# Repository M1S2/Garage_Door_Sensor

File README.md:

# Garage Door Sensor

This is a project to send the status of multiple garage doors (or equal) to one indoor station. This is useful if the door can't be seen from inside.
Each device (sensor and indoor station) uses an ESP12-F (ESP8266) controller that runs the software and is the WiFi transmitter. The data between the sensor and the indoor station is transmitted using ESP-Now. The indoor station acts as a gateway between ESP-Now and WiFi.

## Building the Indoor Station
You need to build only one indoor station. It receives the state of all door sensors. The current version of the indoor station is capable of displaying 2 sensors at the same time. If you need more sensors, the indoor station must be adapted.

### PCBs and Housing
The PCBs are designed using Autodesk Fusion360 to be manufactured with toner transfer method. All design files are located in the [Electrical files for IndoorStation](IndoorStation/Electrical) subfolder.

The housing parts are also designed using Autodesk Fusion360 to be manufactured with a 3D printer. All files are located in the [Mechanical files for IndoorStation](IndoorStation/Mechanical) subfolder. Each part is needed once except the Stand (needed twice).

Also the following additional parts are necessary:
- 4x Screw M3x20
- 2x Screw M3x10
- 6x Heat Insert M3x5x5
- some acrylic glass to cover and diffuse the LEDs
- DC Power Supply (voltage e.g. 5V, is regulated down to 3.3V)

The following image shows all parts of the IndoorStation:

### Software
The software files are located in the [Software files for IndoorStation](IndoorStation/Software) subfolder.

To build and flash the lastest software to the IndoorStation ESP12-F download and install Visual Studio Code and install the PlatformIO extension. The following page explains the whole process: https://randomnerdtutorials.com/vs-code-platformio-ide-esp32-esp8266-arduino/

The following parts must be flashed:
- Firmware: Use the `Build` and `Upload` PlatformIO tasks.
- Filesystem (containing the website files): Use the `Build Filesystem Image` and `Upload Filesystem Image` PlatformIO tasks.

## Building the Sensor
You need to build one sensor per door to monitor. The current version of the indoor station is capable of displaying 2 sensors at the same time. If you need more sensors, the indoor station must be adapted. No changes to the sensor are necessary.
### PCBs and Housing
The PCBs are designed using Autodesk Fusion360 to be manufactured with toner transfer method. All design files are located in the [Electrical files for sensor](Sensor/Electrical) subfolder.

The housing parts are also designed using Autodesk Fusion360 to be manufactured with a 3D printer. All files are located in the [Mechanical files for sensor](Sensor/Mechanical) subfolder. Each part is needed once.

Also the following additional parts are necessary:
- 4x Screw M3x30
- 4x Heat Inserts M3x5x5
- 1x Li-Ion 18650 (e.g. https://www.roboter-bausatz.de/p/bak-18650-lithium-ionen-akku-2900mah-3-6v-3-7v-erhoehter-pluspol)
- 1x Charge Modul USB-C (e.g. https://www.roboter-bausatz.de/p/lithium-batterie-lademodul-usb-c-ip2312-4-2v-5v)
- 2x Magnet for Door Mount

The following image shows all parts of the Sensor:

### Software
The software files are located in the [Software files for Sensor](Sensor/Software) subfolder.

To build and flash the lastest software to the sensor ESP12-F download and install Visual Studio Code and install the PlatformIO extension. The following page explains the whole process: https://randomnerdtutorials.com/vs-code-platformio-ide-esp32-esp8266-arduino/

## Usage
This chapter describes the basic usage of the indoor station and sensor. It is necessary to build at least one device each before proceding.
### Charging the sensor
Switch off the sensor via the switch on the back side and connect it to an USB-C charger. Make sure the charger is capable of delivering enough energy. Otherwise the charging process will be slow.

Charger LED states:

|LED		|Meaning		|
|---------------|-----------------------|
|Red solid	|Powered via USB-C	|
|Green solid	|Charging complete	|

### WiFi Setup
The indoor station isn't yet connected to your local WiFi the first time you use it or after a reset.
It is necessary to connect it to the WiFi. Otherwise the following steps can't be done and the indoor station can't receive the sensor messages.
1. Power the indoor station.
2. The WiFi LED will start flashing blue for about 5 seconds (indicating that it's trying to set up a connection).
3. After this timeout, the WiFi LED will change to white, indicating that the indoor station entered access point configuration mode.
4. Search for all available WiFi networks with your smartphone or computer and connect to the one called "Garagen Tor Status AP" (configuration access point).
5. After connecting to the configuration access point, a captive portal pops up automatically (sometimes needs some seconds; otherwise directly open the IP 192.168.4.1 in your browser).
6. Select your routers WiFi network and enter the password.
7. After confirmation, the indoor station restarts and the WiFi LED is flashing blue again until the connection to the router is established.
8. When successfully connected to the WiFi, the WiFi LED is solid blue.

### Pairing of the Sensor
The pairing of the sensor can be done via the pairing button of the indoor station and the pairing button of the corresponding sensor.
1. Press the pairing button on the indoor station long. The first sensor led will start to flash blue and red.
2. Press the pairing button on the indoor station short to select the sensor slot you want to pair.
3. When the indoor station mode for the correct sensor is pairing, press and hold the pairing button on the sensor for at least 5 seconds (sensor must be switched on).
4. If the pairing of the sensor was successful, the indoor station stopped to flash blue and red.

Repeat all steps for all sensors.

**Alternative:**

The pairing of the sensor can also be done via the web pages of the indoor station.
1. Open the web page (with one of the following ways):
   a) Enter the IP address that was assigned by your router in the address bar of your browser.
   b) For Fritz!Box: enter the following host name in the address bar of your browser: `garagen-tor-status.fritz.box` (or scan the QR code below)
2. Change to the configuration page (gear icon)
3. Enter the MAC address of the sensor to pair in the textbox of the corresponding sensor and click submit.
4. All messages of this sensor are now received for the sensor index where the MAC address was entered.

Repeat steps 3. and 4. for all sensors.

### Mounting the Sensor and Magnet
To mount the sensor and magnet to the garage door:
1. Insert a magnet inside the `Magnet_Mount` part and assemble the `Magnet_Mount_Lid` with a screw.
2. Take the full assembled sensor, the `Door_Mount` part and the `Magnet_Mount`.
3. Switch off the sensor using the switch on the back side.
4. Go inside the garage and close the door.
5. Fix the `Door_Mount` part with double sided tape or power stripes to the door frame. Make sure, there is a small gap of about 3 mm to the metal blade of the door (the outermost moving part). An example position is shown in the following pictures:
6. Insert the sensor in the `Door_Mount`. The two magnets on the `Door_Mount` hold the sensor in place. The counterparts are the two upper screws in the sensor housing.
7. Fix the `Magnet_Mount` part with double sided tape or power stripes to the door blade. Make sure, the magnet is near the icon on the side of the sensor (indicating the position of the reed switch).
8. Open and close the door to make sure, the magnet is moved from and to the sensor, without any mechanical contact. If the door is closed, the magnet must reside near the sensor again.
9. Remove the sensor from the `Door_Mount`, switch the sensor on using the switch on the back side and insert the sensor in the `Door_Mount` again.

<p>
  </img>
  </img>
</p>

### Testing
To test the whole system, open and close one garage door after another and monitor the displayed state on the indoor station.
- When the first door is closed, the LED "1" on the indoor station will be red.
- When the first door is open, the LED "1" on the indoor station will be green.
- When the second door is closed, the LED "2" on the indoor station will be red.
- When the second door is open, the LED "2" on the indoor station will be green.
- All actual door states can also be monitored via the web page (overview page). To open the the web page, follow the steps at the ["Pairing the sensor" chapter](#pairing-of-the-sensor).

## LED States
| Led		         | Color 	    | State    | Description						                                    |
|----------------|------------|----------|------------------------------------------------------------|
| Sensor #1 / #2 | red 		    | solid    | Door is closed, battery ok 				                        |
| Sensor #1 / #2 | red 		    | flashing | Door is closed, battery empty 				                      |
| Sensor #1 / #2 | green 	    | solid    | Door is open, battery ok 					                        |
| Sensor #1 / #2 | green 	    | flashing | Door is open, battery empty 				                        |
| Sensor #1 / #2 | purple 	  | solid    | Sensor mode is charging 					                          |
| Sensor #1 / #2 | red / blue	| blinking | Sensor mode is pairing 					                          |
| Sensor #1 / #2 | / 		      |  off     | Either no message received yet, or sensor mode is disabled |
| Wifi  	       | blue 	    | flashing | Trying to connect to WiFi 				                        	|
| Wifi  	       | blue 	    | solid    | Connected to WiFi 					                                |
| Wifi  	       | red 		    | solid    | Connection to WiFi failed 				                          |
| Wifi  	       | white 	    | solid    | Configuration access point is open 			                  |
| All  		       | yellow 	  | blinking | OTA Update is in progress 					                        |
| All  		       | green 	    | solid    | OTA Update is in ready 					                          |
| All  		       | red 		    | solid    | OTA Update is in failed 					                          |

## Button Reactions:
| Button  | Click Type  | Precondition                            | Description                                                                 |
|---------|-------------|-----------------------------------------|-----------------------------------------------------------------------------|
| Reset   | long press  | always                                  | Memory data and WiFi credentials are erased                                 |
| Pairing | long press  | no sensor is in pairing mode            | Set first sensor to pairing mode (start pairing)                            |
| Pairing | long press  | at least one sensor is in pairing mode  | Set all sensors that are in pairing mode back to normal mode (end pairing)  |
| Pairing | short click | no sensor is in pairing mode            | Do nothing                                                                  |
| Pairing | short click | at least one sensor is in pairing mode  | Find the first sensor with pairing mode. Set it to normal mode and set the next sensor to pairing mode. If it was the last sensor begin with the first again. |

## Sensor Modes
| Mode 		      | Description 													                                                                                                				|
|---------------|-----------------------------------------------------------------------------------------------------------------------------------------------|
| Normal	      | All messages are received, everything is saved, LED on								                                                                  			|
| Disabled	    | All messages are ignored, nothing is saved, LED off										                                                                    		|
| Charging	    | All messages are ignored, nothing is saved, LED in different color								                                                        		|
| Only Display  | Messages are only displayed via the LED, nothing is saved											                                                                |
| Pairing	      | Message from Indoor Station to corresponding sensor to configure the MAC address in the sensor, LED flashes red and blue, nothing is saved	  |

## Developer Hints
- The sensor is designed to consume as less power as possible. Therefore the ESP8266 on the sensor is only switched on when the pin state changed and only as long until the data is sent to the indoor station.
- The sensor trys to send the data on all available WiFi channels until success. The most common used channels are tried first.
- The indoor station can be updated using over the air (OTA) updates. The first time the firmware must be flashed via serial, the OTA is available by navigating to `garagen-tor-status.fritz.box/update` in the browser.
- Accessing the indoor station web pages via the IP address (e.g. 192.168.x.x) isn't really intuitive. The FritzBox offers the possibility to alternatively navigate to `garagen-tor-status.fritz.box`. The correct IP address is then resolved via DNS.

## Further Improvements
- Move the pairing button of the Indoor Station to the backside of the housing (not used very often, cleaner front side) 
- Remove ConnectorLid of Indoor Station housing (software updates are possible via OTA, no need to open the housing very often)
- Remove the on/off switch from the Indoor Station PCB (not really used, disconnecting power supply is enough)

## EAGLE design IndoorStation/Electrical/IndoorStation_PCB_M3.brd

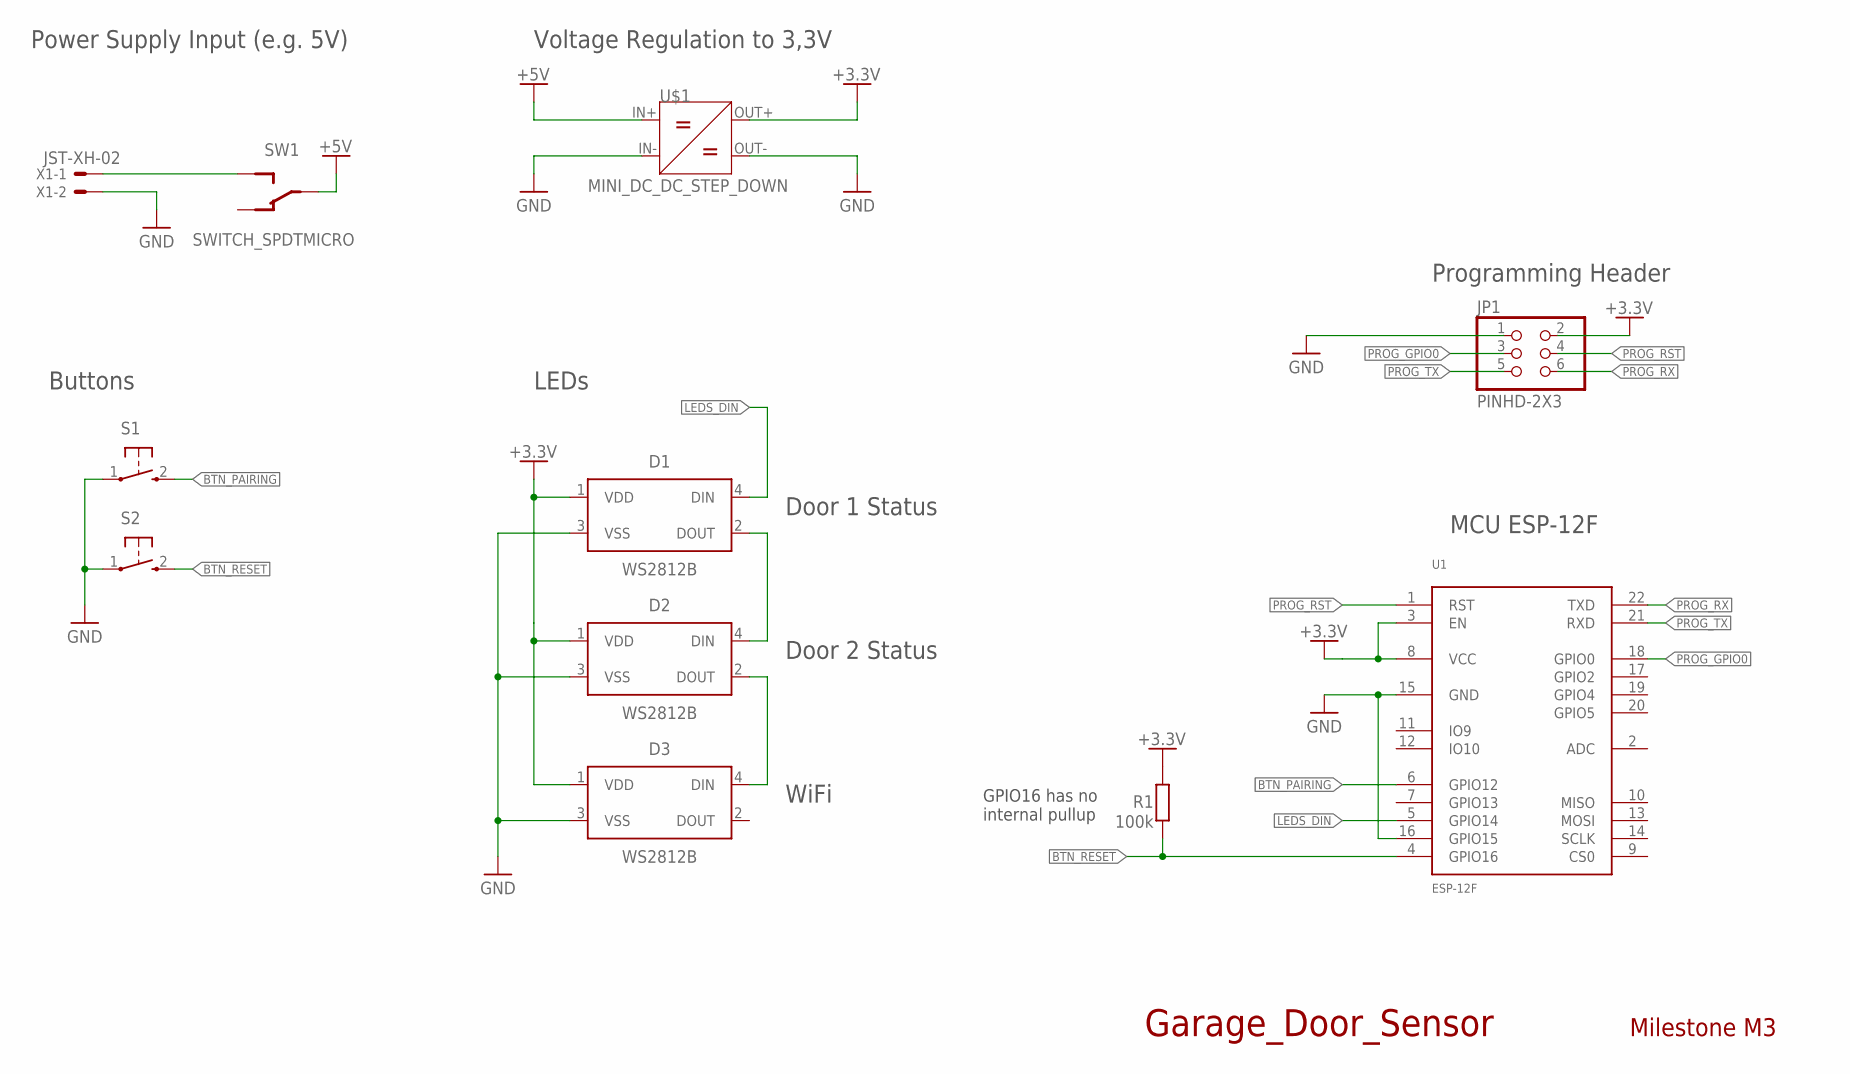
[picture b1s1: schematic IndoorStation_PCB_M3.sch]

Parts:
D1, D2, D3: WS2812B
JP1: PINHD-2X3; 2X03
R1: 100k; R0805
S1, S2: KURZHUBTASTER; B3F-10XX
SW1: SWITCH_SPDTMICRO; MICROSWITCH_SPDT
U1: ESP-12F
U$1: MINI_DC_DC_STEP_DOWN
X1: JST-XH-02; JST-XH-02-EDGE

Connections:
+3.3V: D1.1 (VDD), D2.1 (VDD), D3.1 (VDD), JP1.2, R1.2, U1.3 (EN), U1.8 (VCC), U$1.OUT+
+5V: SW1.P$2, U$1.IN+
BTN_PAIRING: S1.2 (S), U1.6 (GPIO12)
BTN_RESET: R1.1, S2.2 (S), U1.4 (GPIO16)
GND: D1.3 (VSS), D2.3 (VSS), D3.3 (VSS), JP1.1, S1.1, S2.1, U1.15 (GND), U1.16 (GPIO15), U$1.IN-, U$1.OUT-, X1.P$2
LEDS_DIN: D1.4 (DIN), U1.5 (GPIO14)
unnamed: D1.2 (DOUT), D2.4 (DIN)
unnamed: D2.2 (DOUT), D3.4 (DIN)
unnamed: SW1.P$1, X1.P$1
PROG_GPIO0: JP1.3, U1.18 (GPIO0)
PROG_RST: JP1.4, U1.1 (RST)
PROG_RX: JP1.6, U1.22 (TXD)
PROG_TX: JP1.5, U1.21 (RXD)

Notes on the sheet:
Power Supply Input (e.g. 5V)
Programming Header
MCU ESP-12F
Voltage Regulation to 3,3V
Buttons
LEDs
WiFi
Door 1 Status
Door 2 Status
Garage_Door_Sensor
Milestone M3
GPIO16 has no internal pullup

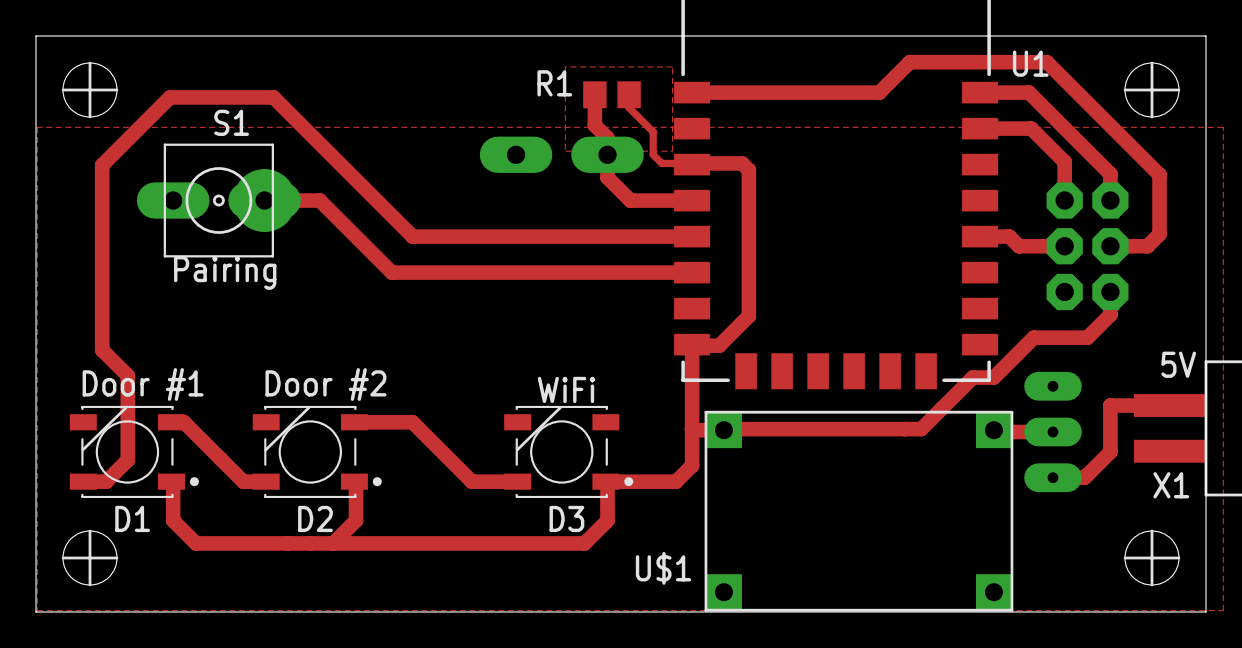
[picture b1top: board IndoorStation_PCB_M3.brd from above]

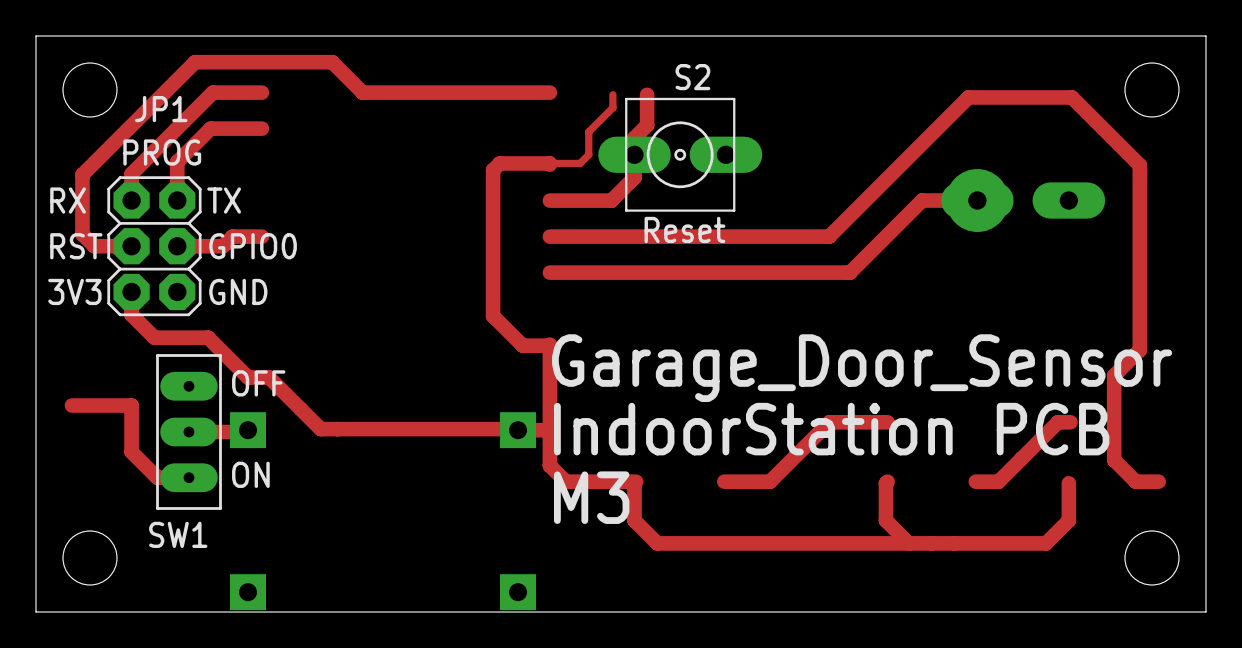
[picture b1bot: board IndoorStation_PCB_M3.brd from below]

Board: 2 copper layers, 65.0 x 32.0 mm, 11 parts (3 on the bottom side), 13 nets.

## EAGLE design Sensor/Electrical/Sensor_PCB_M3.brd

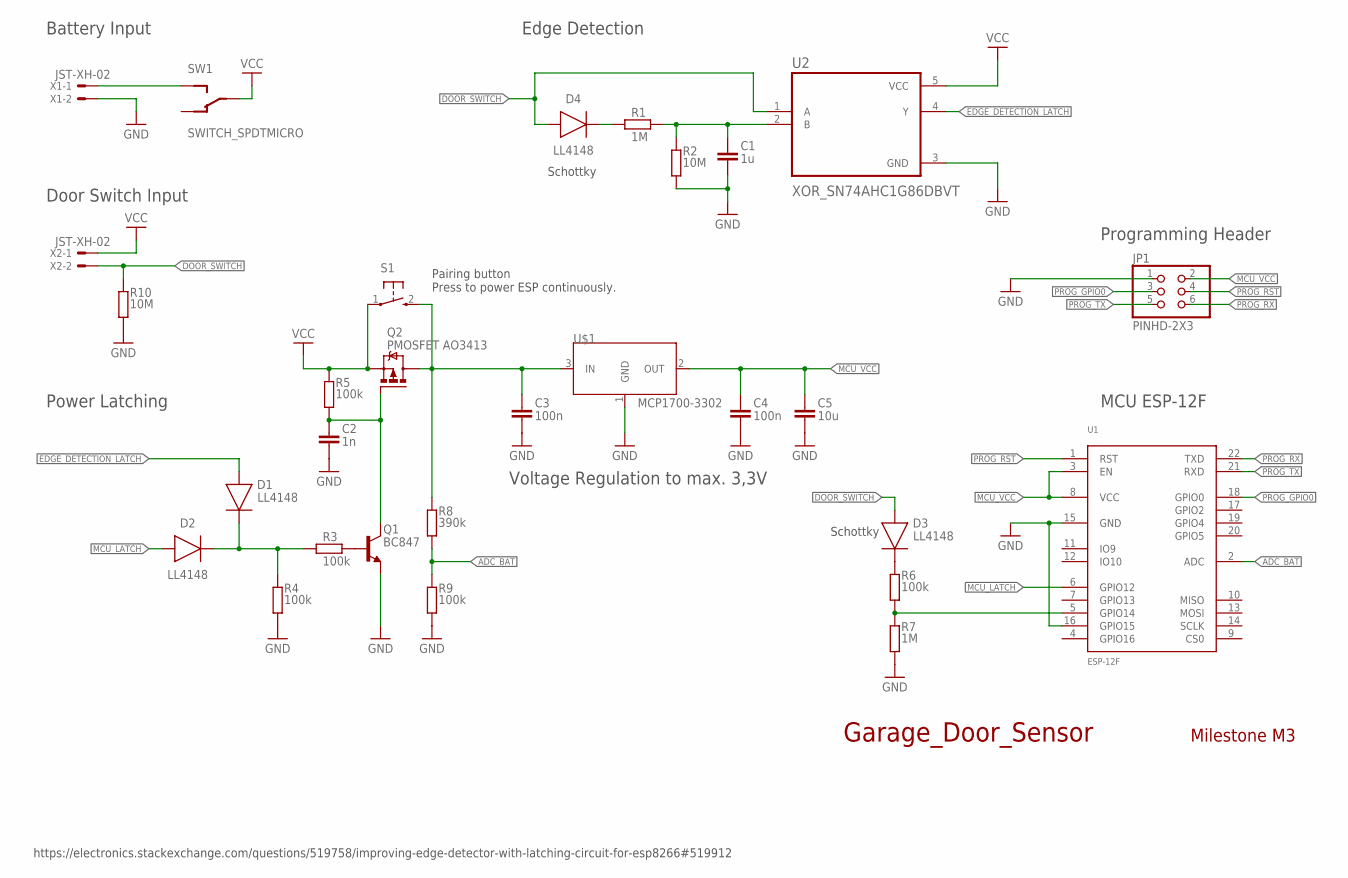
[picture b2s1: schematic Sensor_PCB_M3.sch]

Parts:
C1: 1u; CAPC2012X110
C2: 1n; CAPC2012X110
C3, C4: 100n; CAPC2012X110
C5: 10u; CAPC2012X110
D1, D2, D3, D4: LL4148; DIOMELF3516
JP1: PINHD-2X3; 2X03
Q1: BC847; SOT95P237X112-3N
Q2: PMOSFET AO3413; SOT23
R1, R7: 1M; R0805
R2, R10: 10M; R0805
R3, R4, R5, R6, R9: 100k; R0805
R8: 390k; R0805
S1: KURZHUBTASTER; B3F-10XX
SW1: SWITCH_SPDTMICRO; MICROSWITCH_SPDT
U1: ESP-12F
U2: XOR_SN74AHC1G86DBVT; SOT95P280X145-5N
U$1: MCP1700-3302; SOT23
X1, X2: JST-XH-02; JST-XH-02-PACKAGE-LONG-PAD

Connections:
ADC_BAT: R8.1, R9.2, U1.2 (ADC)
DOOR_SWITCH: D3.2 (A), D4.2 (A), R10.2, U2.1 (A), X2.2
EDGE_DETECTION_LATCH: D1.2 (A), U2.4 (Y)
GND: C1.2, C2.2, C3.2, C4.2, C5.2, JP1.1, Q1.2 (E), R2.1, R4.1, R7.1, R9.1, R10.1, U1.15 (GND), U1.16 (GPIO15), U2.3 (GND), U$1.1 (GND), X1.2
MCU_LATCH: D2.2 (A), U1.6 (GPIO12)
MCU_VCC: C4.1, C5.1, JP1.2, U1.3 (EN), U1.8 (VCC), U$1.2 (OUT)
unnamed: C1.1, R1.2, R2.2, U2.2 (B)
unnamed: D4.1 (C), R1.1
unnamed: Q1.1 (B), R3.2
unnamed: D1.1 (C), D2.1 (C), R3.1, R4.2
unnamed: C2.1, Q1.3 (C), Q2.1 (G), R5.1
unnamed: D3.1 (C), R6.2
unnamed: R6.1, R7.2, U1.5 (GPIO14)
unnamed: SW1.P$1, X1.1
unnamed: C3.1, Q2.3 (D), R8.2, S1.2 (S), U$1.3 (IN)
PROG_GPIO0: JP1.3, U1.18 (GPIO0)
PROG_RST: JP1.4, U1.1 (RST)
PROG_RX: JP1.6, U1.22 (TXD)
PROG_TX: JP1.5, U1.21 (RXD)
VCC: Q2.2 (S), R5.2, S1.1, SW1.P$2, U2.5 (VCC), X2.1

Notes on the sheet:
Battery Input
Door Switch Input
Edge Detection
Power Latching
Programming Header
MCU ESP-12F
https://electronics.stackexchange.com/questions/519758/improving-edge-detector-with-latching-circuit-for-esp8266#519912
Voltage Regulation to max. 3,3V
Pairing button Press to power ESP continuously.
Milestone M3
Garage_Door_Sensor
Schottky

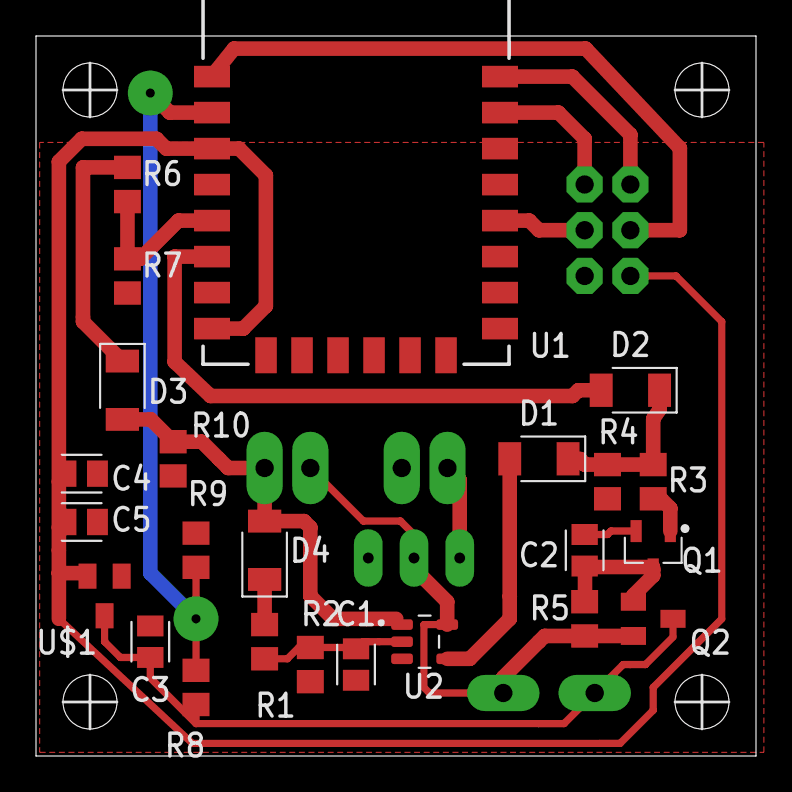
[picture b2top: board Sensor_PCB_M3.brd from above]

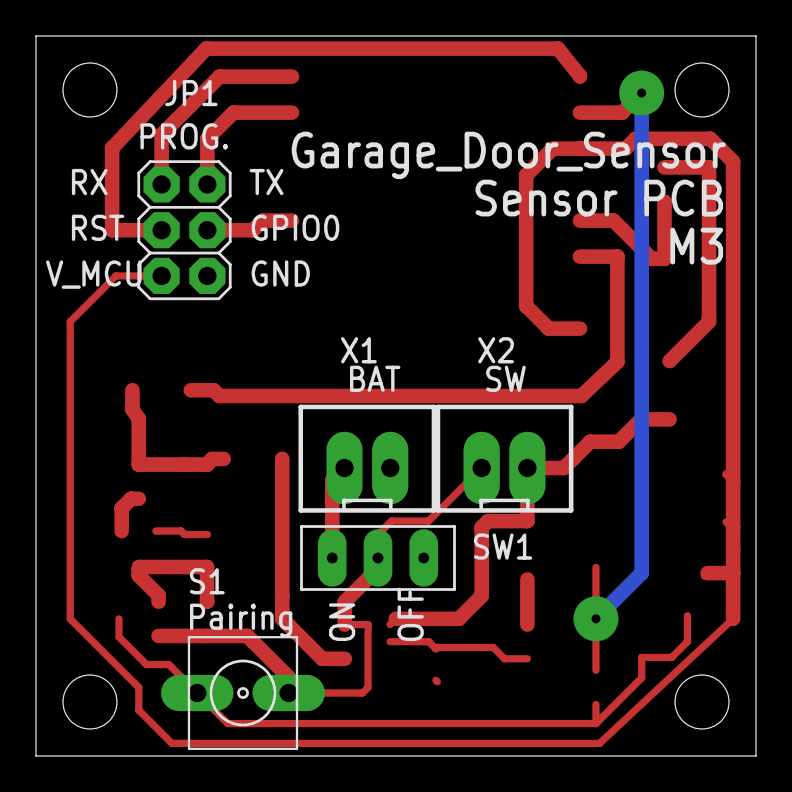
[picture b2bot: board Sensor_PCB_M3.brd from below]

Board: 2 copper layers, 40.0 x 40.0 mm, 29 parts (5 on the bottom side), 20 nets.

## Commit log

2023-12-16 First commit containing the initial code for both the sensor and indoor station
2023-12-19 Added states for build in LED for debugging
2023-12-22 Updated sensor code (try to send data multiple times if not successful at the first try)
2023-12-22 Updated indoor station code (include WS2812B library)
2023-12-27 Updated indoor station code (added web server code)
2024-01-11 Added MCU_LATCH_PIN for Sensor, changed message_t to containg numberSendLoops
2024-01-13 Updated sensor code (door switch pin shouldn't have an pullup resistor)
2024-01-14 Added electrical files (milestone M1)
2024-01-19 Updated indoor station code (separated webserver files to LittleFS, added more webserver files)
2024-01-28 Updated indoor station code (Corrected some pin numbers, added initialisation for button pins)
2024-02-02 First semi-working implementation for own WifiManager based on randomnerdtutorial
2024-02-03 Updated indoor station code (Integrated WiFiManger to get rid of credentials in code)
2024-02-06 Updated indoor station code (Added library for basic button handling)
2024-02-06 Updated indoor station code (first sensor pairing constructs)
2024-02-09 Updated indoor station code (improved LED handling by separating to extra files and using WS2812FX library)
2024-02-11 Updated indoor station code (improved sensor pairing control by syncing button presses with website interaction)
2024-02-19 Updated sensor code (loop over all wifi channels while sending data until success)
2024-02-20 First drafts for pairing logic (not working yet)
2024-02-25 Updated sensor code (measure real battery voltage via ADC and resistor divider)
2024-02-28 Adapted the message_sensor_t to a packed structure to reduce the overall size
2024-02-28 Added NTP time, restructured message receive logic from callback to loop
2024-03-01 Added events to detect when the Wifi is disconnected and connected again
2024-03-01 Updated layout and show timestamp on index.html, timestamp sensor messages now
2024-03-02 Added battery voltage conversion to percent
2024-03-02 Restructured code to timeHandling and sensorPairing modules
2024-03-04 Added OTA functionality
2024-03-05 Restructured code to config, structures and wifiHandling modules
2024-03-05 First working draft for memory module (save last received sensor_messages)
2024-03-08 Restructured memory handling to multiple files in LittleFS
2024-03-10 First tries for WPS methods (not working yet)
2024-03-11 Adapted the ESP hostname displayed by the router, corrected Wifi disconnected LED status when AP is open
2024-03-13 First attempts for displaying sensor history data on web page
2024-03-15 Added input fields to enter the sensor MAC addresses, save and load the sensor mac addresses
2024-03-15 Added number of received messages to sensor_info.html
2024-03-15 Removed sensor pairing code
2024-03-15 Localized web pages to German
2024-03-17 Added dark theme for web pages
2024-03-23 Added feature for sensor data download and upload
2024-03-24 Update chart data without server send events (using chunked data now)
2024-03-25 Fixed timezone for charts, improved get_data server endpoint, changed wifi hostname
2024-03-26 Updated electrical files (milestone M2)
2024-03-26 Added mechanical files (milestone M1)
2024-03-26 Added version placeholders for sensor and indoor station, cleaned indoor station code (removed most button handlers, improved some html)
2024-03-27 Removed delay after sensor data sending, display MAC address of sensor on each power up
2024-03-27 First Readme contents
2024-03-27 Added images
2024-03-30 Added memory statistic to website, improved sending of chart data
2024-04-02 Addes some more error handling for webserver endpoints
2024-04-02 Reworked sensor history charts (support chart filtering for dates and sensors now)
2024-04-02 Removed server sent events and insert index.html values via processor
2024-04-04 Improved html pages navigation menu
2024-04-04 Showing some more decimal places for accu percentage
2024-04-04 Show warning on index.html if no MAC was configured for the sensor
2024-04-05 Improved navigation menu again (better useability for mobile)
2024-04-06 Sending software version from sensor to indoor station and display it on the web pages
2024-04-10 Added sensor modes
2024-04-12 Changed style for sensor mode combo boxes
2024-04-14 Bugfix for chart update (only first sensor values were displayed correctly)
2024-04-14 Added Readme content
2024-04-14 Averaging sensor ADC measurements
2024-04-14 Cleaned up code
2024-04-14 Created release SW_v1.0
2024-05-06 Updated electrical files (milestone M3)
2024-05-17 Added mechanical files (milestone M2)
2024-05-18 Reactivated and renamed button to select pairing mode
2024-05-18 Added feature to pair sensor with indoor station (send sensor MAC to indoor station)
2024-05-18 Improved sensor code (combine methods to send pairing and status data, switch off and on Wifi to improve ADC accuracy)
2024-05-20 Updated Readme and some images
2024-05-20 Created release SW_v2.0
2024-05-20 Update README.md (color for charging LED)
2024-05-22 Make sure that all data is displayed in all charts after updating
2024-05-24 Updated some images for Readme
2024-05-24 Removed data labels from Indoor Station charts
2024-05-24 Bugfixes for reset of indoor station
2024-05-24 Created release SW_v2.1
2024-05-25 Added mechanical files (milestone M3)
2024-05-27 Added Changelog files
2024-07-06 Added DEBUG_OUTPUT define for IndoorStation code, disabled DEBUG_OUTPUT for sensor to save power
2024-07-06 Created release SW_v2.2
2024-07-20 Added some hints for further improvements and a QR code for the indoor station web page to the Readme
2024-07-21 Updated QR code image (smaller QR code with lower redundance), added .stl files to print the QR code for the indoor station
2024-07-28 Added hint to Readme to disable the DNS Rebinding Protection for faster web page response
2024-08-05 Bugfix for sensor_history.js (chart was incomplete or contained wrong data when incomplete chunks were received)
2024-08-07 Added version tag for the webpages
2024-08-07 Created release SW_v2.3
2024-08-23 Adapted Readme (removed DNS rebinding hint as this wasn't helping)
2026-03-12 Added infrastructure for faster testing of the webserver html files (without ESP)
2026-03-16 Adapted chart appearance for sensor_history webpage (disable animations, use stepped line and disable grouping for pinState chart), added logic to only return a specific portion of the sensor_history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
2026-03-18 Reworked /get_data endpoint on ESP (sometimes with date filters no messages were sent)
2026-03-27 Added possibility to debug into indoor station websites inside VS Code
2026-03-27 Adapted logic to only return a specific portion of the sensor_history (radio buttons for date ranges)
2026-03-27 Added dialog to confirm deletion of sensor data (and changed /remove_data endpoint to HTTP_POST)
2026-03-29 Changed website handling to dynamically generate the number of sensor cards and chart series retreived from the ESP
2026-03-29 Show system time on webpage (#1)
2026-03-29 Show icons for loading, inactive or pairing sensor state on overview page (#3), different small bugfixes
2026-03-30 Moved upload data functionality on webpages to each sensor and added mock_server functionality for upload
2026-03-30 SensorIndex was sometimes 1-based (now it's 0-based everywhere)
2026-03-30 Changed display style for buttons and mac address save on management webpage
2026-03-30 Corrected upload endpoint logic on ESP, small webpage adaptions
2026-04-01 Added some checks to ESP code (invalid sensor files or indices)
2026-04-04 First drafts for broadcasting tests (not working!)
2026-04-06 Improved sensor pairing logic (sensor can query the indoor station mac via a access point now during pairing, pairing info save in the Sensor EEPROM)
2026-04-06 Indoor Station: Only allow one sensor slot in pairing mode at the same time
2026-04-06 Persist the configured sensor modes, small bugfix for index webpage
2026-04-07 Update webpage after sensor pairing or when new message received
2026-04-07 Added icons for sensor modes, update webpages on sensor mode changes
2026-04-09 Changed memory format used to persist the system configuration (sensor macs, sensor modes, ...)
2026-04-09 Simplified webpage request handlers
2026-04-09 Adapted indentation for indoor station main.cpp, preparation for encryption keys
2026-04-12 Added sensor message encryption (#5)
2026-04-14 Added feature to assign names to the sensor slots (#8)
2026-04-14 Removed MAC address from indoor station info
2026-04-16 Bugfix for corrupted sensor messages (only add encrypted sensors as peers, unencrypted data is received directly), added size check for received data (#13)
2026-04-16 Restructured system_management webpage layout and added possibility to remove a sensor (#7), disabled data grouping for accu chart
2026-04-17 Made low battery threshold configurable and show warning icon on index.html (#11), removed voltage info from index.html
2026-06-28 Removed possibility to set the MAC address manually (will be done during pairing process)
2026-06-28 Created release SW_v3.0
2026-06-29 Bugfix to update the LED states of the indoor station after pairing success
